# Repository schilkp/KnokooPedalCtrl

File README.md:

# KnokooPedalCtrl

A small modification that allows the Knokoo FES150 Fume Extractor to be turned on
and off using a 1/4" foot pedal.

## Why?

The way my bench is setup, I cannot comfortably reach the speed control/power knob.
Life's very difficult, tell me about it. 

But because I know myself well enough to know that I won't use this (or any) fume extractor
if I have to crawl on the floor every time I want to solder something, this small project
was born.

It is also not the quietest machine, so being able to turn it on and off only when actually 
soldering has made using it much more pleasant. 

## How?

This small PIC12F1572-based board sits between the Knokoo's Main PCB and the front intensity knob.  

The Knokoo turns itself off when the intensity knob is turned all the way off.
This board interrupts the 5V rail normally provided to the potentiometer by the Knokoo PCB, and only
enables it when the foot pedal is pressed.

This way the Intensity Knob can permanently be left set to the desired intensity, and the pedal can
be used to turn the unit on and off. 

Pressing the pedal once turns the unit on and starts a timer controlled by the position of a second
potentiometer. The unit will shut off when either the timer runs out or the pedal is pressed again.

Pressing the pedal twice in short succession turns the unit on permanently until the pedal is pressed
again.

If the pedal is unplugged, the board will disable itself and the unit will function as before.

## Installation

[will follow shortly]

## Slight Modifications

### No Timer Potentiometer

Instead of a second potentiometer, the timer duration can also be permanently fixed using resistors R6 and R7.  

The duration will be approx `(15)*(R6/(R6+R7)` minutes

(R6+R7) should be 10K at least. The pins where the potentiometer would otherwise be connected to should be left disconnected.

### No Pedal Detect

If the jack for the pedal does not have a switch, PEDC should be connected to GND (for example to POT-).

Of course, in this case, the unit will not return to normal operation when no pedal is connected.

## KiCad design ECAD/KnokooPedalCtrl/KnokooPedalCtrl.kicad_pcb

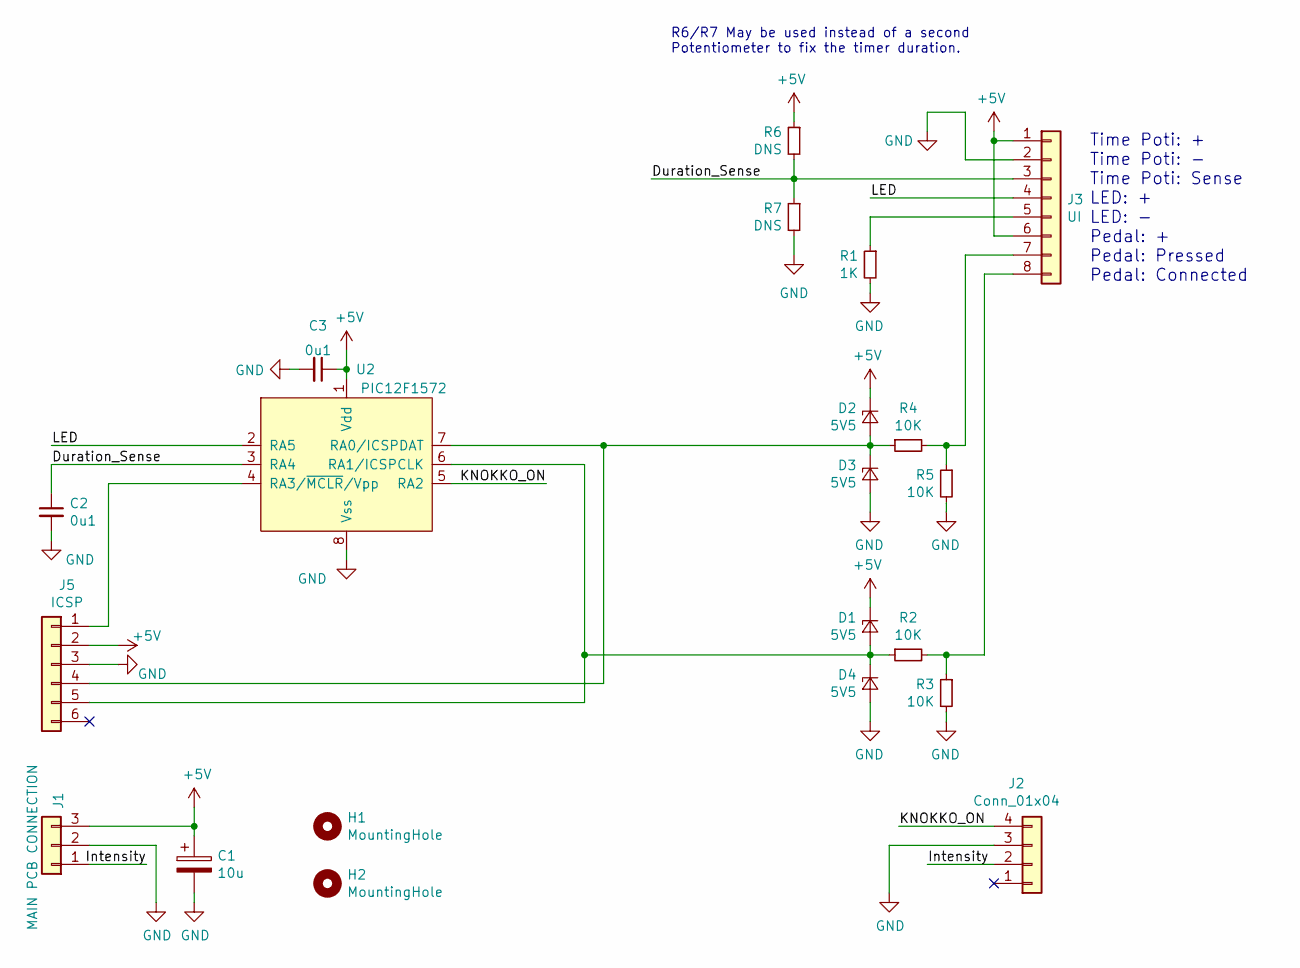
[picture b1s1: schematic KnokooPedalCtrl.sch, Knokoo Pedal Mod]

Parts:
C1: 10u; CP_Elec_6.3x7.7
C2, C3: 0u1; C_0603_1608Metric
D1, D2, D3, D4: 5V5; D_SOD-123
H1, H2: MountingHole; MountingHole_3.2mm_M3_Pad_Via
J1: MAIN PCB CONNECTION; JST_XH_S3B-XH-A_1x03_P2.50mm_Horizontal
J2: Conn_01x04; JST_XH_S4B-XH-A_1x04_P2.50mm_Horizontal
J3: UI; JST_XH_S8B-XH-A_1x08_P2.50mm_Horizontal
J5: ICSP; PinHeader_1x06_P2.54mm_Vertical
R1: 1K; R_0603_1608Metric
R2, R3, R4, R5: 10K; R_0603_1608Metric
R6, R7: DNS; R_0603_1608Metric
U2: PIC12F1572; SOIC-8_3.9x4.9mm_P1.27mm

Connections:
+5V: C1.1, C3.1, D1.1 (K), D2.1 (K), J1.3, J3.1, J3.6, J5.2, R6.1, U2.1 (Vdd)
/Duration_Sense: C2.1, J3.3, R6.2, R7.1, U2.3 (RA4)
/Intensity: J1.1, J2.2
/KNOKKO_ON: J2.4, U2.5 (RA2)
/LED: J3.4, U2.2 (RA5)
GND: C1.2, C2.2, C3.2, D3.2 (A), D4.2 (A), J1.2, J2.3, J3.2, J5.3, R1.2, R3.2, R5.2, R7.2, U2.8 (Vss)
unnamed: D1.2 (A), D4.1 (K), J5.5, R2.1, U2.6 (RA1/ICSPCLK)
unnamed: D2.2 (A), D3.1 (K), J5.4, R4.1, U2.7 (RA0/ICSPDAT)
unnamed: J3.5, R1.1
unnamed: J3.7, R4.2, R5.1
unnamed: J3.8, R2.2, R3.1
unnamed: J5.1, U2.4 (RA3/~MCLR~/Vpp)

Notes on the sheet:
Time Poti: + Time Poti: - Time Poti: Sense LED: + LED: - Pedal: + Pedal: Pressed Pedal: Connected
R6/R7 May be used instead of a second Potentiometer to fix the timer duration.

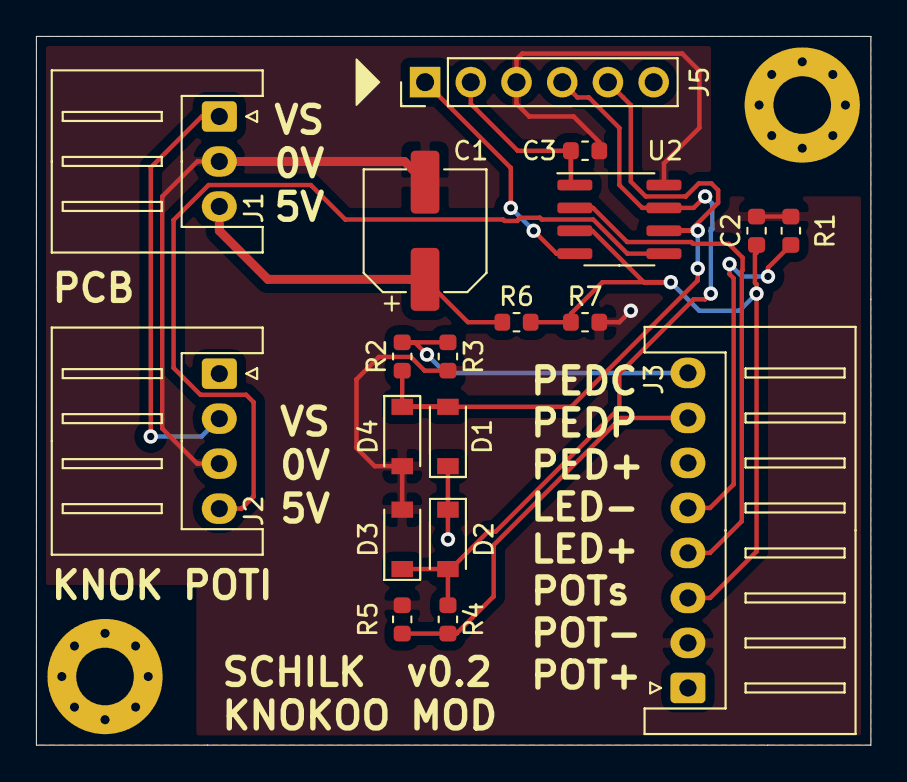
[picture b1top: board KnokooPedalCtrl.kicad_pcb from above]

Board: 2 copper layers, 46.4 x 39.4 mm, 21 parts (0 on the bottom side), 12 nets.

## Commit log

2020-09-26 Added PCB v0.0
2020-09-26 First firmware draft.
2020-10-17 v0.1
    Small pinout and silkscreen fixes
2020-11-01 v0.2
2020-11-01 First draft Documentation
2021-01-07 Readme Typos
2021-09-06 Small Documentation Updates
